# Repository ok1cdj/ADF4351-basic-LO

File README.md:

# ADF4351-basic-LO
Very simple software for PLL ADF4351 and ATTiny13  can be compiled with arduino and microcore
https://github.com/MCUdude/MicroCore

v 0.2 Ondra OK1CDJ 5/2020 ondra@ok1cdj.com
 
ADF4351 eval board from eBay or Ali for aprox. 17 USD. 
 
Please check the ADF4351 datasheet or use ADF4351 software
to get proper PLL register values.

# ADF4351-Beacon
Simple CW beacon. SW is also for ATTiny13 now or can use ATTINY45/85 on same PCB.
Beacon send string in morse code like - OK1CDJ JO70VA and then continous tone for 5s.

# ADF4351-Key
Version with external keying on PB0 of ATTiny13. Can be used as simple CW transmitter.

## PIN layout of ATTINY13/45/85
MCU is powered  by 3.3V directly from PLL board.

 pin 5 - PB0 external keying - optional

 pin 3 - PB4  to ADF4531 clock (CLK) 
 
 pin 2 - PB3 to ADF4531 data (DATA) 
 
 pin 7 - PB2 to ADF4531 latch enable (LE) 

Kit is available here:

https://www.hamshop.cz/pll-adf4351-c51/adf4351-ovladani-s-attiny13-stavebnice-i351/

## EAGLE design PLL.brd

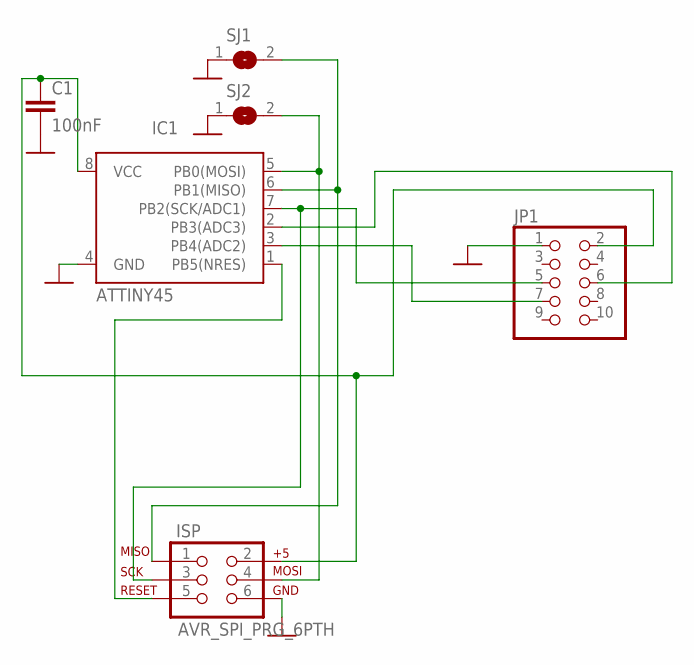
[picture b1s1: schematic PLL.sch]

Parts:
C1: 100nF; C0805
IC1: ATTINY45; SO08-EIAJ
ISP: AVR_SPI_PRG_6PTH; 2X3
JP1: PINHD-2X5; 2X05
SJ1, SJ2: SJ

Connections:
GND: C1.2, IC1.4 (GND), ISP.6, JP1.1, SJ1.1, SJ2.1
ISP: IC1.7 (PB2(SCK/ADC1)), ISP.3, JP1.5
unnamed: IC1.3 (PB4(ADC2)), JP1.7
unnamed: IC1.2 (PB3(ADC3)), JP1.6
unnamed: C1.1, IC1.8 (VCC), ISP.2, JP1.2
unnamed: IC1.6 (PB1(MISO)), ISP.1, SJ1.2
unnamed: IC1.5 (PB0(MOSI)), ISP.4, SJ2.2
unnamed: IC1.1 (PB5(NRES)), ISP.5

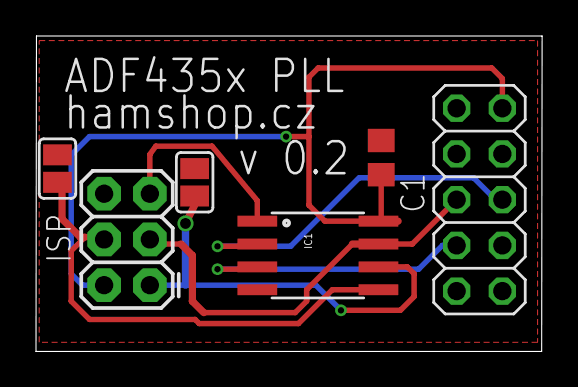
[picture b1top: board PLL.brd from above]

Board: 2 copper layers, 28.1 x 17.5 mm, 6 parts (0 on the bottom side), 8 nets.

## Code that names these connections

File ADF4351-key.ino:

/* Very simple software for PLL ADF4351 and ATTiny13
  can be compiled with arduino and microcore
  https://github.com/MCUdude/MicroCore
  v 0.1 Ondra OK1CDJ 5/2020 ondra@ok1cdj.com
  
  Parts of this code is based on routines written by PA3FYM

  Please check the ADF4351 datasheet or use ADF4351 software
  to get PLL register values.

  PIN layout
  PB0 key input - keyed low
  PB4 ADF4531 clock (CLK)
  PB3 ADF4531 data (DATA)
  PB2 ADF4531 latch enable (LE)
*/





// PLL registers
long int r0, r1, r2, r3, r4, r5;
#define KEY 0
int val = 0;

////////////////////////////////////////////////////////
void write2PLL(uint32_t PLLword) {         // clocks 32 bits word  directly to the ADF4351
  // msb (b31) first, lsb (b0) last
  for (byte i = 32; i > 0; i--) { // PLL word 32 bits
    (PLLword & 0x80000000 ? PORTB |= 0b00001001 : PORTB &= 0b11110111);  // data on PB3
    PORTB |= 0b00010001;                   // clock in bit on rising edge of CLK (PB4 = 1)
    PORTB &= 0b11101111;                   // CLK (PB4 = 0)
    PLLword <<= 1;                         // rotate left for next bit
  }
  PORTB |= 0b00000101;                   // latch in PLL word on rising edge of LE (PB2 = 1)
  PORTB &= 0b11111011;  // LE (PB2 = 0)
  delayMicroseconds(1);
}

void setup () {

  DDRB  = 0xfe; // PB are all outputs PB0 input
  PORTB = 0x01; // make PB low and PB0 high

  // Fout= 2450.050 only from main port

  r0 = 0x300008;
  r1 = 0x8008FA1;


  r2 = 0x4E42;
  r3 = 0x4B3;
  r4 = 0x8C803C;
  r5 = 0x580005;



  // write from r5 to r0
  write2PLL(r5);
  write2PLL(r4);
  write2PLL(r3);
  write2PLL(r2);
  write2PLL(r1);
  write2PLL(r0);

}

// main loop
void loop() {
  val = digitalRead(KEY);
  // TX ON/OFF can be used for CW keying
  if (val == 1)
    write2PLL(r4 & 0xffffffdf); //txoff
  else
    write2PLL(r4); //txon


}

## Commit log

2018-09-12 Schematic and PCB in EAGLE CAD
2018-09-12 Complete board
2018-09-19 Create ADF4351-Beacon.ino
    Simple CW beacon
2018-09-19 Update README.md
    Added cw beacon sw.
2020-05-12 Create ADF4351-key.ino
    Version with external keying on PB0
2020-10-07 Beacon which fit in ATTINY13. Mods by OK1VSR
